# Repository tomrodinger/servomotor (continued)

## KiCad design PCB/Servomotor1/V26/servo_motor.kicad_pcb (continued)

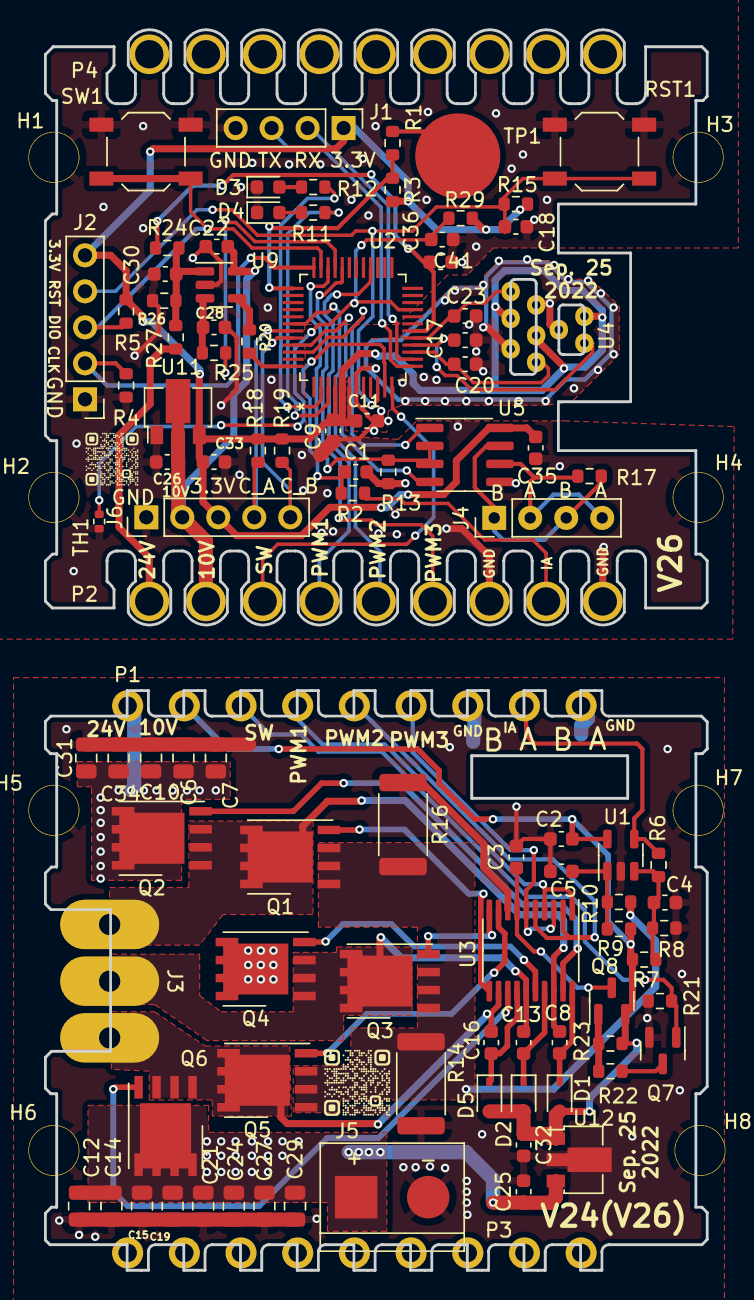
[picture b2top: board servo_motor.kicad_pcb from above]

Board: 2 copper layers, 46.7 x 87.5 mm, 108 parts (0 on the bottom side), 61 nets.

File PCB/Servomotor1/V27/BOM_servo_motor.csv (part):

Source:,G:\OneDrive\Work\Upwork\TomRodinger\servo_motor_V27\servo_motor.kicad_sch,,,,,,,,,,
Date:,6/16/2023 9:41,,,,,,,,,,
Tool:,Eeschema 7.0.1,,,,,,,,,,
Generator:,C:\Program Files\KiCad\7.0\bin\scripting\plugins/bom_csv_grouped_by_value.py,,,,,,,,,,
Component Count:,108,,,,,,,,,,
,,,,,,,,,,,
Collated Components:,,,,,,,,,,,
,,,,,,,,,,,
Item,Qty,Reference(s),Value,LibPart,Footprint,Datasheet,DNP,Description,LCSC,MN,MPN
1,3,"C1, C5, C30",100pF,Device:C,Capacitor_SMD:C_0603_1608Metric,~,,50V 100pF C0G ±5% 0603  Multilayer Ceramic Capacitors MLCC - SMD/SMT ROHS,C14858,Samsung Electro-Mechanics,CL10C101JB8NNNC
2,5,"C2, C22, C26, C32, C41",1uF,Device:C,Capacitor_SMD:C_0603_1608Metric,~,,50V 1uF X5R ±10% 0603  Multilayer Ceramic Capacitors MLCC - SMD/SMT ROHS,C15849,Samsung Electro-Mechanics,CL10A105KB8NNNC
3,2,"C3, C11",4.7uF,Device:C,Capacitor_SMD:C_0603_1608Metric,~,,16V 4.7uF X5R ±10% 0603  Multilayer Ceramic Capacitors MLCC - SMD/SMT ROHS,C19666,Samsung Electro-Mechanics,CL10A475KO8NNNC
4,1,C4,NC,Device:C,Capacitor_SMD:C_0603_1608Metric,~,,NC,,,
5,13,"C6, C7, C10, C12, C14, C15, C19, C21, C24, C27, C29, C31, C34",10uF,Device:C,Capacitor_SMD:C_0805_2012Metric,~,,50V 10uF X5R ±10% 0805  Multilayer Ceramic Capacitors MLCC - SMD/SMT ROHS,C440198,Murata Electronics,GRM21BR61H106KE43L
6,9,"C8, C9, C13, C16, C18, C25, C28, C35, C36",100nF,Device:C,Capacitor_SMD:C_0603_1608Metric,~,,50V 100nF X7R ±10% 0603  Multilayer Ceramic Capacitors MLCC - SMD/SMT ROHS,C14663,YAGEO,CC0603KRX7R9BB104
7,3,"C17, C20, C23",1nF,Device:C,Capacitor_SMD:C_0603_1608Metric,~,,50V 1nF X7R ±10% 0603  Multilayer Ceramic Capacitors MLCC - SMD/SMT ROHS,C1588,Samsung Electro-Mechanics,CL10B102KB8NNNC
8,1,C33,10uF,Device:C,Capacitor_SMD:C_0603_1608Metric,~,,10V 10uF X5R ±10% 0603  Multilayer Ceramic Capacitors MLCC - SMD/SMT ROHS,C19702,Samsung Electro-Mechanics,CL10A106KP8NNNC
9,1,D1,1N4148WS,:1N4148WS_1,Diode_SMD:D_SOD-323,https://www.vishay.com/docs/85751/1n4148ws.pdf,,100V 200mW Single 1.25V@150mA 4ns 150mA SOD-323  Switching Diode ROHS,C2128,"Jiangsu Changjing Electronics Technology Co., Ltd.",1N4148WS
10,2,"D2, D5",1N4148WS,Diode:1N4148WS,Diode_SMD:D_SOD-323,https://www.vishay.com/docs/85751/1n4148ws.pdf,,100V 200mW Single 1.25V@150mA 4ns 150mA SOD-323  Switching Diode ROHS,C2128,"Jiangsu Changjing Electronics Technology Co., Ltd.",1N4148WS
11,1,D3,KT-0603R,Device:LED,LED_SMD:LED_0603_1608Metric,~,,Red 0603 Light Emitting Diodes,C2286,"Jiangsu Changjing Electronics Technology Co., Ltd.",1N4148WS
12,1,D4,19-217/GHC-YR1S2/3T,Device:LED,LED_SMD:LED_0603_1608Metric,~,,LED GREEN CLEAR SMD,C72043,Hubei KENTO Elec,KT-0603R
13,8,"H1, H2, H3, H4, H5, H6, H7, H8",MountingHole_Pad,Mechanical:MountingHole_Pad,servo_motor:Mounting Hole 3.5mm,~,,MountingHole_Pad,,,
14,1,J1,Serial Port,Connector:Conn_01x04_Male,Connector_PinHeader_2.54mm:PinHeader_1x04_P2.54mm_Vertical,~,, 2.54mm Plugin Black 1x4P Plugin,C2691448,XFCN,PZ254V-11-04P
15,1,J2,Programming,Connector:Conn_01x05_Male,Connector_PinHeader_2.54mm:PinHeader_1x05_P2.54mm_Vertical,~,,2.54mm Plugin Black Brass 1x5P Plugin,C492404,XFCN,PZ254V-11-05P
16,1,J3,Screw_Terminal_01x03,Connector:Screw_Terminal_01x03,servo_motor:MOTOR,~,,Screw_Terminal_01x03,,,
17,1,J4,RS485,Connector:Conn_01x04_Male,Connector_PinHeader_2.54mm:PinHeader_1x04_P2.54mm_Vertical,~,,2.54mm Plugin Black 1x4P Plugin,C2691448,XFCN,PZ254V-11-04P
18,1,J5,Power IN,Connector:Conn_01x02_Male,TerminalBlock:TerminalBlock_bornier-2_P5.08mm,~,,P=5.08mm Screw termina,C8465,Ningbo Kangnex Elec,WJ500V-5.08-2P
19,1,J6,Encoder,Connector:Conn_01x05_Male,Connector_PinHeader_2.54mm:PinHeader_1x05_P2.54mm_Vertical,~,,2.54mm Plugin Black Brass 1x5P Plugin,C492404,XFCN,PZ254V-11-05P
20,2,"P1, P3",Board_to_Board_Connector,servo_motor:Board_to_Board_Connector,servo_motor:board_to_board_male,,,Board_to_Board_Connector,,,
21,2,"P2, P4",Board_to_Board_Connector,servo_motor:Board_to_Board_Connector,servo_motor:board_to_board_female,,,Board_to_Board_Connector,,,
22,6,"Q1, Q2, Q3, Q4, Q5, Q6",CRTM025N03L,servo_motor:CRTM025N03L,servo_motor:CRTM025N03L,,,"30V 98A 2.5mΩ@10V,50A 2.5W N Channel DFN-8-EP(6x5)",C467170,CRMICRO,CRTM025N03L
23,1,Q7,MMBT3904,Transistor_BJT:MMBT3904,Package_TO_SOT_SMD:SOT-23,https://www.onsemi.com/pub/Collateral/2N3903-D.PDF,,"40V 200mW 100@10mA,1V 200mA NPN SOT-23",C20526,Jiangsu Changjing,MMBT3904
24,1,Q8,2N3906,Transistor_BJT:2N3906,Package_TO_SOT_SMD:SOT-23,https://www.onsemi.com/pub/Collateral/2N3906-D.PDF,,"40V 350mW 100@10mA,1V 200mA PNP SOT-23",C147294,KEC Semicon,2N3906S-RTK/P
25,1,R1,1M,Device:R,Resistor_SMD:R_0603_1608Metric,~,,100mW Thick Film Resistors ±1% 1MΩ 0603  Chip Resistor - Surface Mount ROHS,C22935,UNI-ROYAL(Uniroyal Elec),0603WAF1004T5E
26,2,"R2, R29",4.7K,Device:R,Resistor_SMD:R_0603_1608Metric,~,,100mW Thick Film Resistors ±1% 4.7kΩ 0603  Chip Resistor - Surface Mount ROHS,C23162,UNI-ROYAL(Uniroyal Elec),0603WAF4701T5E
27,1,R3,10M,Device:R,Resistor_SMD:R_0603_1608Metric,~,,100mW Thick Film Resistors ±1% 10MΩ 0603  Chip Resistor - Surface Mount ROHS,C7250,UNI-ROYAL(Uniroyal Elec),0603WAF1005T5E
28,14,"R4, R5, R8, R10, R13, R15, R17, R20, R21, R22, R23, R24, R25, R27",10K,Device:R,Resistor_SMD:R_0603_1608Metric,~,,100mW Thick Film Resistors ±100ppm/℃ ±1% 10kΩ 0603  Chip Resistor - Surface Mount ROHS,C25804,UNI-ROYAL(Uniroyal Elec),0603WAF1002T5E
29,1,R6,33K,Device:R,Resistor_SMD:R_0603_1608Metric,~,,100mW Thick Film Resistors ±1% 33kΩ 0603  Chip Resistor - Surface Mount ROHS,C4216,UNI-ROYAL(Uniroyal Elec),0603WAF3302T5E
30,1,R7,680K,Device:R,Resistor_SMD:R_0603_1608Metric,~,,100mW Thick Film Resistors ±1% 680kΩ 0603  Chip Resistor - Surface Mount ROHS,C25822,UNI-ROYAL(Uniroyal Elec),0603WAF6803T5E
31,1,R9,300K,Device:R,Resistor_SMD:R_0603_1608Metric,~,,100mW Thick Film Resistors ±1% 300kΩ 0603  Chip Resistor - Surface Mount ROHS,C23024,UNI-ROYAL(Uniroyal Elec),0603WAF3003T5E
32,1,R11,470,Device:R,Resistor_SMD:R_0603_1608Metric,~,,100mW Thick Film Resistors ±1% 470Ω 0603  Chip Resistor - Surface Mount ROHS,C23179,UNI-ROYAL(Uniroyal Elec),0603WAF4700T5E
33,3,"R12, R18, R19",1.5K,Device:R,Resistor_SMD:R_0603_1608Metric,~,,100mW Thick Film Resistors ±1% 1.5kΩ 0603  Chip Resistor - Surface Mount ROHS,C22843,UNI-ROYAL(Uniroyal Elec),0603WAF1501T5E
34,2,"R14, R16",25121WF100MT4E,Device:R,Resistor_SMD:R_2512_6332Metric,~,,"1W 10mΩ ±800ppm/℃ ±1% 2512 Current Sense Resistors""",C127692,UNI-ROYAL(Uniroyal Elec),25121WF100MT4E
35,1,R26,1K,Device:R,Resistor_SMD:R_0603_1608Metric,~,,100mW Thick Film Resistors ±1% 1kΩ 0603  Chip Resistor - Surface Mount ROHS,C21190,UNI-ROYAL(Uniroyal Elec),0603WAF1001T5E
36,2,"RST1, SW1",TS-1187A-B-A-B,Switch:SW_Push,Button_Switch_SMD:SW_SPST_TL3342,~,, SPST SMD Tactile Switches,C318884,XKB Connectivity,TS-1187A-B-A-B
37,1,TH1,100k 1% NTC,Device:Thermistor_NTC,Resistor_SMD:R_0402_1005Metric,~,,THERM NTC 100KOHM 4250K 0402,C77130,Murata Electronics,NCP15WF104F03RC
38,1,TP1,TestPoint,Connector:TestPoint,servo_motor:TestPoint 6mm,~,,TestPoint,,,
39,2,"U1, U9",LM321,Amplifier_Operational:LM321,Package_TO_SOT_SMD:SOT-23-5,http://www.ti.com/lit/ds/symlink/lm321.pdf,,IC OPAMP GP 1 CIRCUIT SOT23-5,C471859,Texas Instruments,LM321LVIDBVR
40,1,U2,STM32G030C8T6,dual_extruder:STM32G030C8T6,servo_motor:STM32G030C8T6,,,IC MCU 32BIT 64KB FLASH 48LQFP,C529329,STMicroelectronics,STM32G030C8T6
41,1,U3,EG2133,dual_extruder:EG2133,Package_SO:TSSOP-20_4.4x6.5mm_P0.65mm,,,TSSOP-20 Gate Drive ICs ,C190343,EG Micro,EG2133
42,1,U4,Hall_Sensor*3,servo_motor:Hall_Sensor*3,servo_motor:hall_sensor_3,,,Hall_Sensor*3,,,
43,1,U5,SN75176BDR,Interface_UART:SN75176AD,Package_SO:SOIC-8_3.9x4.9mm_P1.27mm,http://www.ti.com/lit/ds/symlink/sn75176a.pdf,,transceiver 1/1 SOIC-8 RS-485/RS-422 Ics,C7063,Texas Instruments,SN75176BDR
44,1,U11,HT7533-1,Regulator_Linear:HT75xx-1-SOT89,Package_TO_SOT_SMD:SOT-89-3,https://www.holtek.com/documents/10179/116711/HT75xx-1v250.pdf,,100mA Fixed 3.3V~3.3V Positive 30V,C14289,Holtek Semicon,HT7533-1
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
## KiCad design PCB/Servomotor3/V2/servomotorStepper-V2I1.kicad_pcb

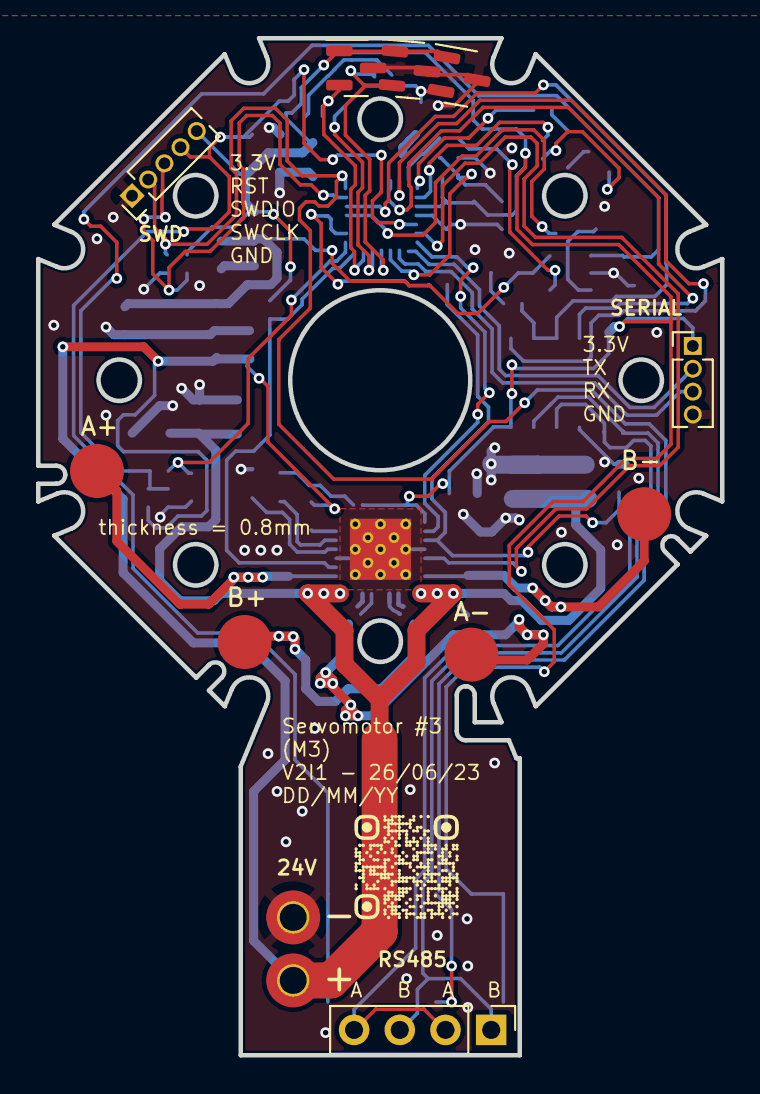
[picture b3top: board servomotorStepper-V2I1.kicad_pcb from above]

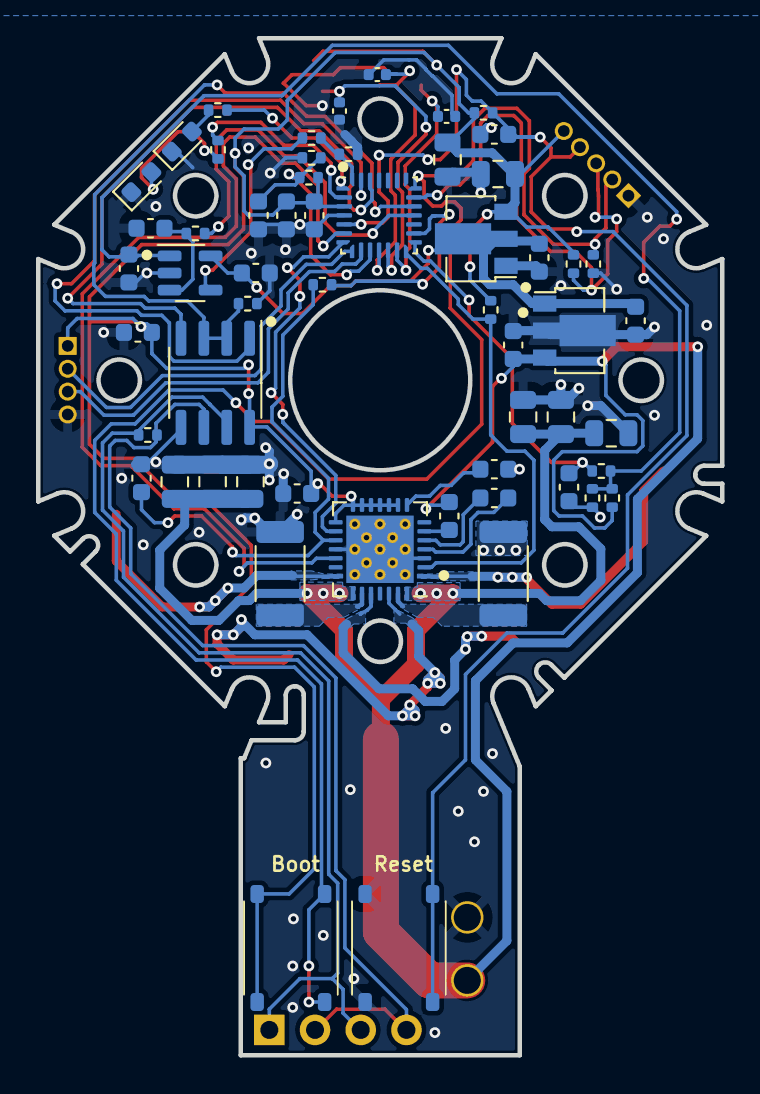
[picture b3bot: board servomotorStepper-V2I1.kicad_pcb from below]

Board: 2 copper layers, 38.0 x 56.5 mm, 69 parts (57 on the bottom side), 43 nets.

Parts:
C1, C2, C3, C18, C25, C28, C35, C36, C37: 100nF; C_0603_1608Metric
C4, C6: 220nF; C_0603_1608Metric
C5, C7, C8, C12, C14, C15, C19, C33: 4.7uF; C_0805_2012Metric
C17, C20, C23: 1nF; C_0402_1005Metric
C22, C26, C32, C41: 1uF; C_0603_1608Metric
C30: 100pF; C_0603_1608Metric
C38: 4.7uF; C_0603_1608Metric
D3: KT-0603R; LED_0603_1608Metric
D4: 19-217/GHC-YR1S2/3T; LED_0603_1608Metric
J1: 01x04 male P=1.27mm; PinHeader_1x04_P1.27mm_Vertical
J2: 01x05 male P=1.27mm; PinHeader_1x05_P1.27mm_Vertical
J3, J6, J7, J8: Conn_01x01_Socket; Pad_3mm_TopOnly
J4: 01x04 male P=2.54mm; PinHeader_1x04_P2.54mm_Vertical
J9, J10: Conn_01x01_Socket; Pad_hole_3mm_TopOnly
R1, R3: 270m; R_2010_5025Metric
R4, R5, R13, R15, R17, R20, R22, R24, R25, R27: 10k; R_0402_1005Metric
R6, R23: 5.6k; R_0402_1005Metric
R11: 470R; R_0402_1005Metric
R12: 1.5k; R_0402_1005Metric
R26: 1K; R_0402_1005Metric
R29: 4.7k; R_0402_1005Metric
SW1, SW2: TS-1187A-B-C-B
TH1: 100k 1% NTC; R_0402_1005Metric
U4, U6, U7: AH49HSC; SOT-23
U5: A4988; QFN-28-1EP_5x5mm_P0.5mm_EP3.75x3.75mm_ThermalVias_0.3mm
U8: STM32G031G8U6; QFN-28_4x4mm_P0.5mm
U9: LM321; SOT-23-5
U10: SP3485EN; SOIC-8_3.9x4.9mm_P1.27mm
U11: HT7533-1; SOT-89-3
U12: L78L10_SOT89; SOT-89-3

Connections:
+3.3V: C5.1, C6.1, C33.1, C35.2, C37.1, C38.1, J1.1, J2.5, R5.2, R6.2, R15.2, R29.2, SW1.1, U4.1 (VCC), U5.9 (MS1), U5.10 (MS2), U5.11 (MS3), U5.12 (~RESET), U5.13 (ROSC), U5.14 (~SLEEP), U5.15 (VDD), U6.1 (VCC), U7.1 (VCC), U8.3 (VDD), U10.8 (VCC), U11.3 (VOUT)
+10V: C22.1, C26.1, C32.1, U9.5 (V+), U11.2 (VIN), U12.1 (OUT)
+24V: C3.1, C7.1, C8.1, C12.1, C14.1, C15.1, C19.1, C25.1, J9.1, R27.1, U5.22 (VBB1), U5.28 (VBB2), U12.3 (IN)
/index/schTop/A: J4.2, J4.4, R17.1, U10.6 (A)
/index/schTop/B: J4.1, J4.3, R17.2, U10.7 (B)
/index/schTop/DIR: U5.19 (DIR), U8.6 (PA0)
/index/schTop/HALL1: C17.1, U7.2 (VOUT), U8.11 (PA5)
/index/schTop/HALL2: C20.1, U6.2 (VOUT), U8.12 (PA6)
/index/schTop/HALL3: C23.1, U4.2 (VOUT), U8.13 (PA7)
/index/schTop/IMCONTROL: R22.1, U8.16 (PA8)
/index/schTop/LED_GREEN: R11.1, U8.2 (PC15)
/index/schTop/LED_RED: R12.1, U8.1 (PC14)
/index/schTop/OUT1A: J7.1, U5.24 (OUT1A)
/index/schTop/OUT1B: J6.1, U5.21 (OUT1B)
/index/schTop/OUT2A: J3.1, U5.26 (OUT2A)
/index/schTop/OUT2B: J8.1, U5.1 (OUT2B)
/index/schTop/OVER_VOLTAGE: R20.2, R23.2, U8.28 (PB8)
/index/schTop/PWMOV: R25.1, U8.18 (PA11/PA9)
/index/schTop/REF24: C36.1, R24.1, U8.15 (PB1)
/index/schTop/RESET: C18.1, J2.4, R15.1, SW2.1, U8.5 (PF2)
/index/schTop/RS485_D: U8.26 (PB6), U10.4 (DI)
/index/schTop/RS485_EN: R13.2, U8.19 (PA12/PA10), U10.2 (~RE), U10.3 (DE)
/index/schTop/RS485_R: U8.27 (PB7), U10.1 (RO)
/index/schTop/STEP: U5.16 (STEP), U8.7 (PA1)
/index/schTop/SWCLK: J2.2, R4.2, SW1.2, U8.21 (PA14)
/index/schTop/SWDIO: J2.3, R5.1, U8.20 (PA13)
/index/schTop/TEMPERATURE: C41.1, R29.1, TH1.1, U8.10 (PA4)
/index/schTop/UART2 RX: J1.3, U8.9 (PA3)
/index/schTop/UART2 TX: J1.2, U8.8 (PA2)
/index/schTop/VREF: C1.1, R22.2, U5.17 (VREF)
/index/schTop/~MENABLE: R6.1, U5.2 (~ENABLE), U8.14 (PB0)
GND: C1.2, C4.1, C5.2, C6.2, C7.2, C8.2, C12.2, C14.2, C15.2, C17.2, C18.2, C19.2, C20.2, C22.2, C23.2, C25.2, C26.2, C28.2, C30.2, C32.2, C33.2, C35.1, C36.2, C37.2, C38.2, C41.2, D3.1 (K), D4.1 (K), J1.4, J2.1, J10.1, R1.1, R3.1, R4.1, R13.1, R23.1, R26.2, SW2.2, TH1.2, U4.3 (GND), U5.3 (GND), U5.18 (GND), U5.29 (PAD), U6.3 (GND), U7.3 (GND), U8.4 (VSS), U9.2 (V-), U10.5 (GND), U11.1 (GND), U12.2 (GND)
unnamed: D3.2 (A), R12.2
unnamed: D4.2 (A), R11.2
unnamed: R20.1, U9.4
unnamed: C2.1, U5.4 (CP1)
unnamed: C2.2, U5.5 (CP2)
unnamed: R1.2, U5.23 (SENSE1)
unnamed: R3.2, U5.27 (SENSE2)
unnamed: C3.2, U5.6 (VCP)
unnamed: C4.2, U5.8 (VREG)
unnamed: C30.1, R24.2, R26.1, R27.2, U9.1 (+)
unnamed: C28.1, R25.2, U9.3 (-)
